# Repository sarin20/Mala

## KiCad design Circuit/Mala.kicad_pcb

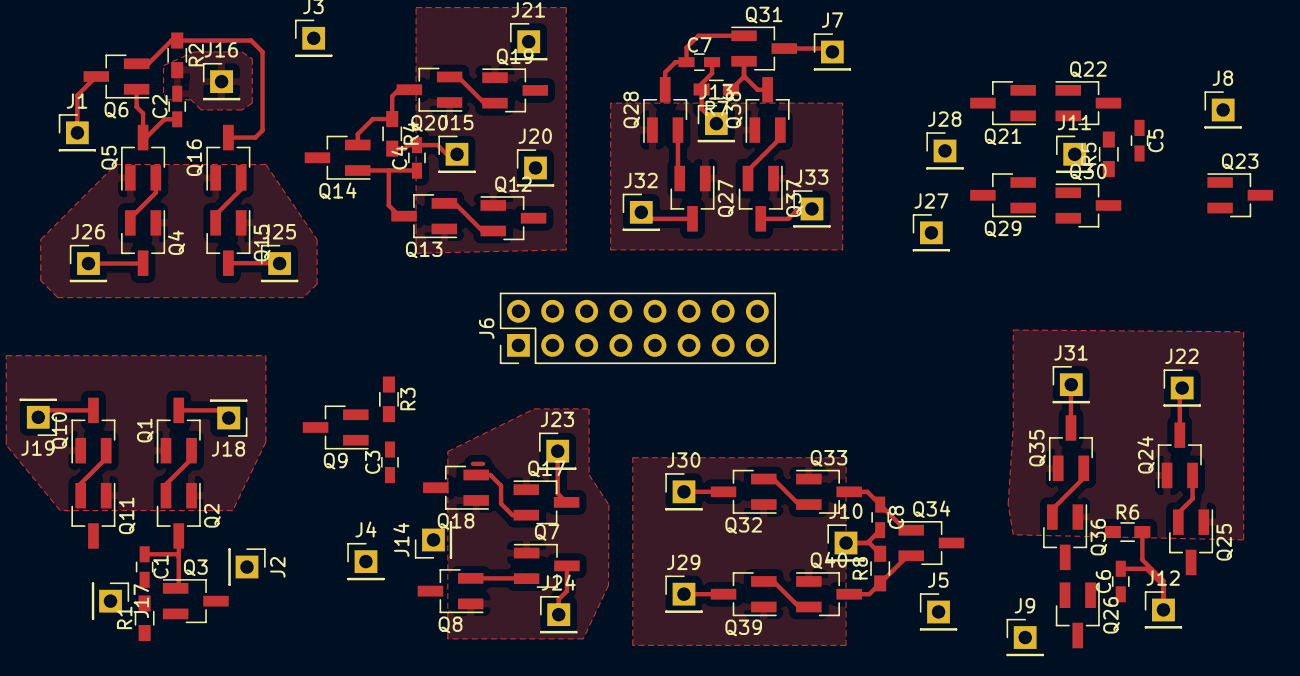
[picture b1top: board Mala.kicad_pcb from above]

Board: 2 copper layers, 89 parts (0 on the bottom side), 51 nets.

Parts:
C1, C2, C3, C4, C5, C6, C7, C8: C; C_0603_HandSoldering
J1, J2, J3, J4, J5, J7, J8, J9, J10, J11, J12, J13, J14, J15, J16, J17, J18, J19, J20, J21, J22, J23, J24, J25, J26, J27, J28, J29, J30, J31, J32, J33: CONN_01X01; Pin_Header_Straight_1x01_Pitch2.54mm
J6: CONN_02X08; Pin_Header_Straight_2x08_Pitch2.54mm
Q1, Q2, Q3, Q4, Q5, Q6, Q7, Q8, Q9, Q10, Q11, Q12, Q13, Q14, Q15, Q16, Q17, Q18, Q19, Q20, Q21, Q22, Q23, Q24, Q25, Q26, Q27, Q28, Q29, Q30, Q31, Q32, Q33, Q34, Q35, Q36, Q37, Q38, Q39, Q40: Q_NMOS_GSD; SOT-23_Handsoldering
R1, R2, R3, R4, R5, R6, R7, R8: R; R_0603_HandSoldering

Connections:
GND: C1.2, C2.2, C3.2, C4.2, C5.2, C6.2, C7.2, C8.2, J6.10, J6.12, J6.13, J6.14, J6.15, J6.16, J10.1, J11.1, J12.1, J13.1, J14.1, J15.1, J16.1, J17.1, R1.2, R2.2, R3.2, R4.2, R5.2, R6.2, R7.2, R8.2
unnamed: C1.1, Q2.3, Q3.1
unnamed: C2.1, Q5.3, Q6.1
unnamed: C3.1, Q8.3, Q9.1
unnamed: C4.1, Q13.3, Q14.1
unnamed: C5.1, Q22.3, Q23.1
unnamed: C6.1, Q25.3, Q26.1
unnamed: C7.1, Q28.3, Q31.1
unnamed: C8.1, Q33.3, Q34.1
unnamed: J1.1, Q6.3
unnamed: J2.1, Q3.3
unnamed: J3.1, Q14.3
unnamed: J4.1, Q9.3
unnamed: J5.1, Q34.3
unnamed: J7.1, Q31.3
unnamed: J8.1, Q23.3
unnamed: J9.1, Q26.3
unnamed: Q1.2, Q2.2
unnamed: Q4.2, Q5.2
unnamed: Q7.2, Q8.2
unnamed: Q10.2, Q11.2
unnamed: Q3.2, Q11.3, R1.1
unnamed: Q12.2, Q13.2
unnamed: Q14.2, Q20.3, R4.1
unnamed: Q15.2, Q16.2
unnamed: Q6.2, Q16.3, R2.1
unnamed: Q17.2, Q18.2
unnamed: Q9.2, Q18.3, R3.1
unnamed: Q19.2, Q20.2
unnamed: Q21.2, Q22.2
unnamed: Q23.2, Q30.3, R5.1
unnamed: Q24.2, Q25.2
unnamed: Q26.2, Q36.3, R6.1
unnamed: Q27.2, Q28.2
unnamed: Q29.2, Q30.2
unnamed: Q31.2, Q38.3, R7.1
unnamed: Q32.2, Q33.2
unnamed: Q34.2, Q40.3, R8.1
unnamed: Q35.2, Q36.2
unnamed: Q37.2, Q38.2
unnamed: Q39.2, Q40.2
Vcntrl: J6.9, J18.1, J20.1, J22.1, J24.1, J26.1, J28.1, J30.1, J32.1, Q1.3, Q4.3, Q7.3, Q12.3, Q21.3, Q24.3, Q27.3, Q32.3
Vfb: J6.11, J19.1, J21.1, J23.1, J25.1, J27.1, J29.1, J31.1, J33.1, Q10.3, Q15.3, Q17.3, Q19.3, Q29.3, Q35.3, Q37.3, Q39.3
С0: J6.1, Q1.1, Q2.1, Q10.1, Q11.1
С1: J6.2, Q4.1, Q5.1, Q15.1, Q16.1
С2: J6.3, Q7.1, Q8.1, Q17.1, Q18.1
С3: J6.4, Q12.1, Q13.1, Q19.1, Q20.1
С4: J6.5, Q32.1, Q33.1, Q39.1, Q40.1
С5: J6.6, Q27.1, Q28.1, Q37.1, Q38.1
С6: J6.7, Q24.1, Q25.1, Q35.1, Q36.1
С7: J6.8, Q21.1, Q22.1, Q29.1, Q30.1

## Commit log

2017-09-24 initial
2017-10-09 3 zones left
2017-10-10 2 zones left
2017-10-17 1 zone left
